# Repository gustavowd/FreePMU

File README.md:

# FreePMU

A Low-Cost, Open Architecture, Synchronized Harmonic Phasor Measurement Unit.

The FreePMU project delivers an open source Phasor Measurement Unit (PMU) for power system analysis based on the STM32F769 Discovery kit and an instrumentation PCB. Its characteristics are low cost, open architecture and open source code. FreePMU measures fundamental and harmonic synchrophasors as well as the signal frequency for a three-phase distribution circuit.

Prototype

# Publications

SEGER, P. V. H.; MORETO, MIGUEL; GRANDO, F. L.; LAZZARETTI, A. E.; DENARDIN, G. W.; PASTRO, C. R. Power System Monitoring Through Low-Voltage Distribution Network Using freePMU. IEEE Transactions on Industry Applications, v. 58, n. 3, p. 3153-3163, 2022.

SEGER, P. V. H.; MORETO, MIGUEL; GRANDO, F. L.; LAZZARETTI, A. E.; DENARDIN, G. W.; PASTRO, C. R. Monitoring Low Voltage Electrical Networks Using Low Cost PMUs: a Case Study. IEEE International Conference on Environment and Electrical Engineering and IEEE Industrial and Commercial Power Systems Europe, 2020, Madrid.

GRANDO, F. L.; DENARDIN, G. W.; MORETO, M.; LAZZARETTI, A. E.; VIEIRA NETO, H. A method for synchronized harmonic phasor measurement based on hardware-enhanced Fast Fourier Transform. International Transactions on Electrical Energy Systems, v. 30, p. 1-19, 2020.

# Configurations

The PMU code has several possible configurations. These settings can be configured in the main.h file.

1. Set the PMU identification number for the communication with PDC

#define PMUID	0x0001

2. Set the utility nominal frequency (50 or 60Hz)

#define NOMINAL_FREQ 60

3. Set the utility nominal voltage (127 or 220V)

#define NOMINAL_VOLTAGE 127

4. Define if harmonics are enable or not

#define ENABLE_HARMONICS 1

5. Set if the oversamling will be used or not (0 or 1)

#define OVERSAMPLING 1

6. Define the GPS baudrate

#define GPS_BAUDRATE 115200

7. Set this define to 1 for simulate GPS time stamp and PPS

#define SIMULATED_GPS 0

8. Defines if the GPS will provide the 30 pulses per second or not (if not defined, GPS will provide 1 pulse per second)

#define PPS_30_HZ

9. Defines if the measure data will be based on peak or RMS values (possible values are RMS_GAIN or PEAK_GAIN)

#define PEAK_OR_RMS	RMS_GAIN

10. Set the transport protocol to communicate with the PDC (TCP_PMU or UDP_PMU)

#define TRANSPORT_PROTOCOL TCP_PMU

11. Several gains for the fit curves (depends on the instrumentation board)

For better performance, such gains must be defined through a calibration process

Interface video

Connections

Used GPS

Used voltage transformer

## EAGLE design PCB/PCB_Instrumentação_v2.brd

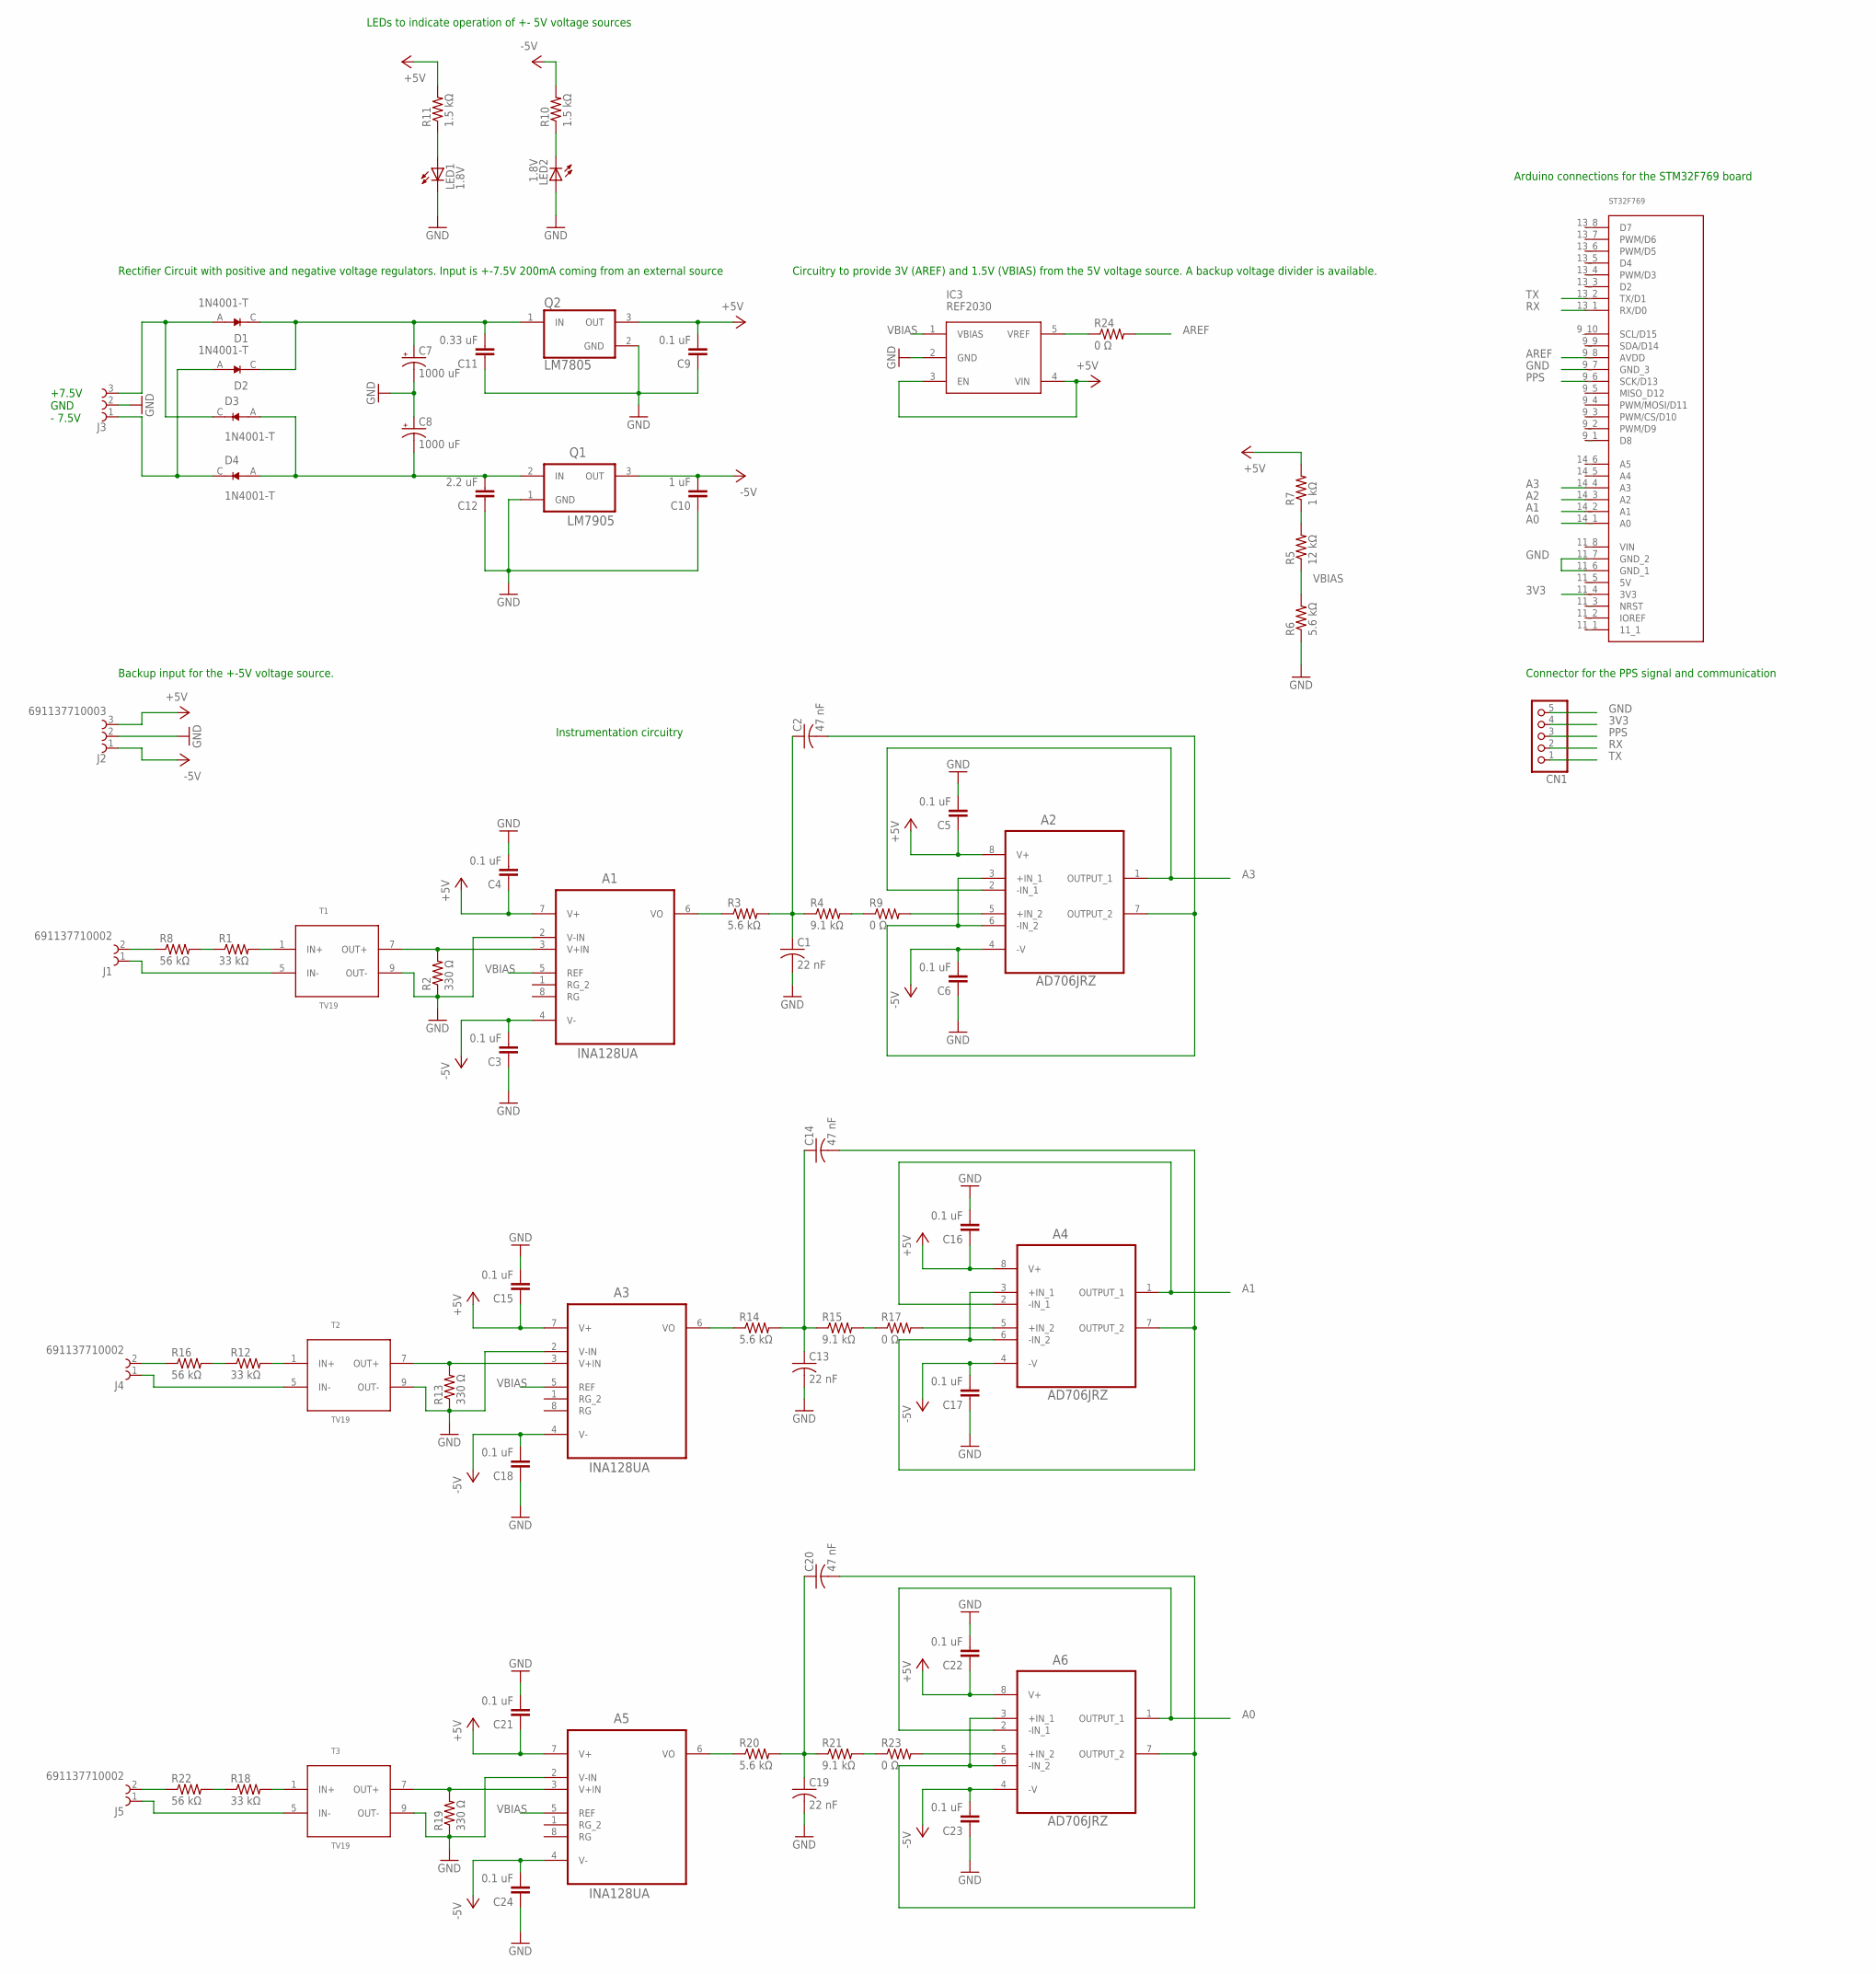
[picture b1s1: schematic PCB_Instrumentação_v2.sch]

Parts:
A1, A3, A5: INA128UA; SOIC127P600X175-8N
A2, A4, A6: AD706JRZ; SOIC127P600X175-8N
C1, C13, C19: 22 nF; C1206
C2, C14, C20: 47 nF; C1206
C3, C4, C5, C6, C9, C15, C16, C17, C18, C21, C22, C23, C24: 0.1 uF; C0805
C7, C8: 1000 uF; E5-10,5
C10: 1 uF; C0805
C11: 0.33 uF; C0805
C12: 2.2 uF; C0805
CN1: PINHD-1X5; 1X05
D1, D2, D3, D4: 1N4001-T; DIOAD953W69L521D272
IC3: REF2030; TSOT-23_S5
J1, J4, J5: 691137710002
J2, J3: 691137710003
LED1, LED2: 1.8V; LED5MM
Q1: LM7905; TO254P450X1020X1935-3P
Q2: LM7805; TO254P1054X470X2600-3
R1, R12, R18: 33 kΩ; 0207/7
R2, R13, R19: 330 Ω; 0207/7
R3, R6, R14, R20: 5.6 kΩ; R1206
R4, R15, R21: 9.1 kΩ; R1206
R5: 12 kΩ; R1206
R7: 1 kΩ; R1206
R8, R16, R22: 56 kΩ; 0207/7
R9, R17, R23, R24: 0 Ω; R1206
R10, R11: 1.5 kΩ; R1206
T1, T2, T3: TV19
U$1: ST32F769

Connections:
3V3: CN1.4, U$1.11_4 (3V3)
+5V: A1.7 (V+), A2.8 (V+), A3.7 (V+), A4.8 (V+), A5.7 (V+), A6.8 (V+), C4.1, C5.1, C9.2, C15.1, C16.1, C21.1, C22.1, IC3.3 (EN), IC3.4 (VIN), J2.3, Q2.3 (OUT), R7.2, R11.2
-5V: A1.4 (V-), A2.4 (-V), A3.4 (V-), A4.4 (-V), A5.4 (V-), A6.4 (-V), C3.2, C6.2, C10.2, C17.2, C18.2, C23.2, C24.2, J2.1, Q1.3 (OUT), R10.2
A0: A6.1 (OUTPUT_1), A6.2 (-IN_1), U$1.14_1 (A0)
A1: A4.1 (OUTPUT_1), A4.2 (-IN_1), U$1.14_2 (A1)
A2: U$1.14_3 (A2)
A3: A2.1 (OUTPUT_1), A2.2 (-IN_1), U$1.14_4 (A3)
AREF: R24.2, U$1.9_8 (AVDD)
GND: A1.2 (V-IN), A3.2 (V-IN), A5.2 (V-IN), C1.2, C3.1, C4.2, C5.2, C6.1, C7.-, C8.+, C9.1, C10.1, C11.1, C12.1, C13.2, C15.2, C16.2, C17.1, C18.1, C19.2, C21.2, C22.2, C23.1, C24.1, CN1.5, IC3.2 (GND), J2.2, J3.2, LED1.K (C), LED2.A, Q1.1 (GND), Q2.2 (GND), R2.1, R6.1, R13.1, R19.1, T1.9 (OUT-), T2.9 (OUT-), T3.9 (OUT-), U$1.9_7 (GND_3), U$1.11_6 (GND_1), U$1.11_7 (GND_2)
unnamed: R1.2, T1.1 (IN+)
unnamed: A1.3 (V+IN), R2.2, T1.7 (OUT+)
unnamed: A1.6 (VO), R3.1
unnamed: C1.1, C2.1, R3.2, R4.1
unnamed: R4.2, R9.1
unnamed: A2.3 (+IN_1), A2.6 (-IN_2), A2.7 (OUTPUT_2), C2.2
unnamed: R5.2, R7.1
unnamed: J1.2, R8.1
unnamed: J1.1, T1.5 (IN-)
unnamed: R1.1, R8.2
unnamed: C7.+, C11.2, D1.C, D2.C, Q2.1 (IN)
unnamed: C8.-, C12.2, D3.A, D4.A, Q1.2 (IN)
unnamed: D2.A, D4.C, J3.1
unnamed: D1.A, D3.C, J3.3
unnamed: A2.5 (+IN_2), R9.2
unnamed: LED1.A, R11.1
unnamed: LED2.K (C), R10.1
unnamed: R12.2, T2.1 (IN+)
unnamed: A3.3 (V+IN), R13.2, T2.7 (OUT+)
unnamed: A3.6 (VO), R14.1
unnamed: C13.1, C14.1, R14.2, R15.1
unnamed: A4.3 (+IN_1), A4.6 (-IN_2), A4.7 (OUTPUT_2), C14.2
unnamed: J4.1, T2.5 (IN-)
unnamed: J4.2, R16.1
unnamed: R12.1, R16.2
unnamed: R15.2, R17.1
unnamed: A4.5 (+IN_2), R17.2
unnamed: R18.2, T3.1 (IN+)
unnamed: A5.3 (V+IN), R19.2, T3.7 (OUT+)
unnamed: A5.6 (VO), R20.1
unnamed: C19.1, C20.1, R20.2, R21.1
unnamed: A6.3 (+IN_1), A6.6 (-IN_2), A6.7 (OUTPUT_2), C20.2
unnamed: J5.1, T3.5 (IN-)
unnamed: J5.2, R22.1
unnamed: R18.1, R22.2
unnamed: R21.2, R23.1
unnamed: A6.5 (+IN_2), R23.2
unnamed: IC3.5 (VREF), R24.1
PPS: CN1.3, U$1.9_6 (SCK/D13)
RX: CN1.2, U$1.13_1 (RX/D0)
TX: CN1.1, U$1.13_2 (TX/D1)
VBIAS: A1.5 (REF), A3.5 (REF), A5.5 (REF), IC3.1 (VBIAS), R5.1, R6.2

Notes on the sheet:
LEDs to indicate operation of +- 5V voltage sources
Rectifier Circuit with positive and negative voltage regulators. Input is +-7.5V 200mA coming from an external source
Circuitry to provide 3V (AREF) and 1.5V (VBIAS) from the 5V voltage source. A backup voltage divider is available.
Arduino connections for the STM32F769 board
Backup input for the +-5V voltage source.
Connector for the PPS signal and communication
Instrumentation circuitry
+7.5V GND - 7.5V

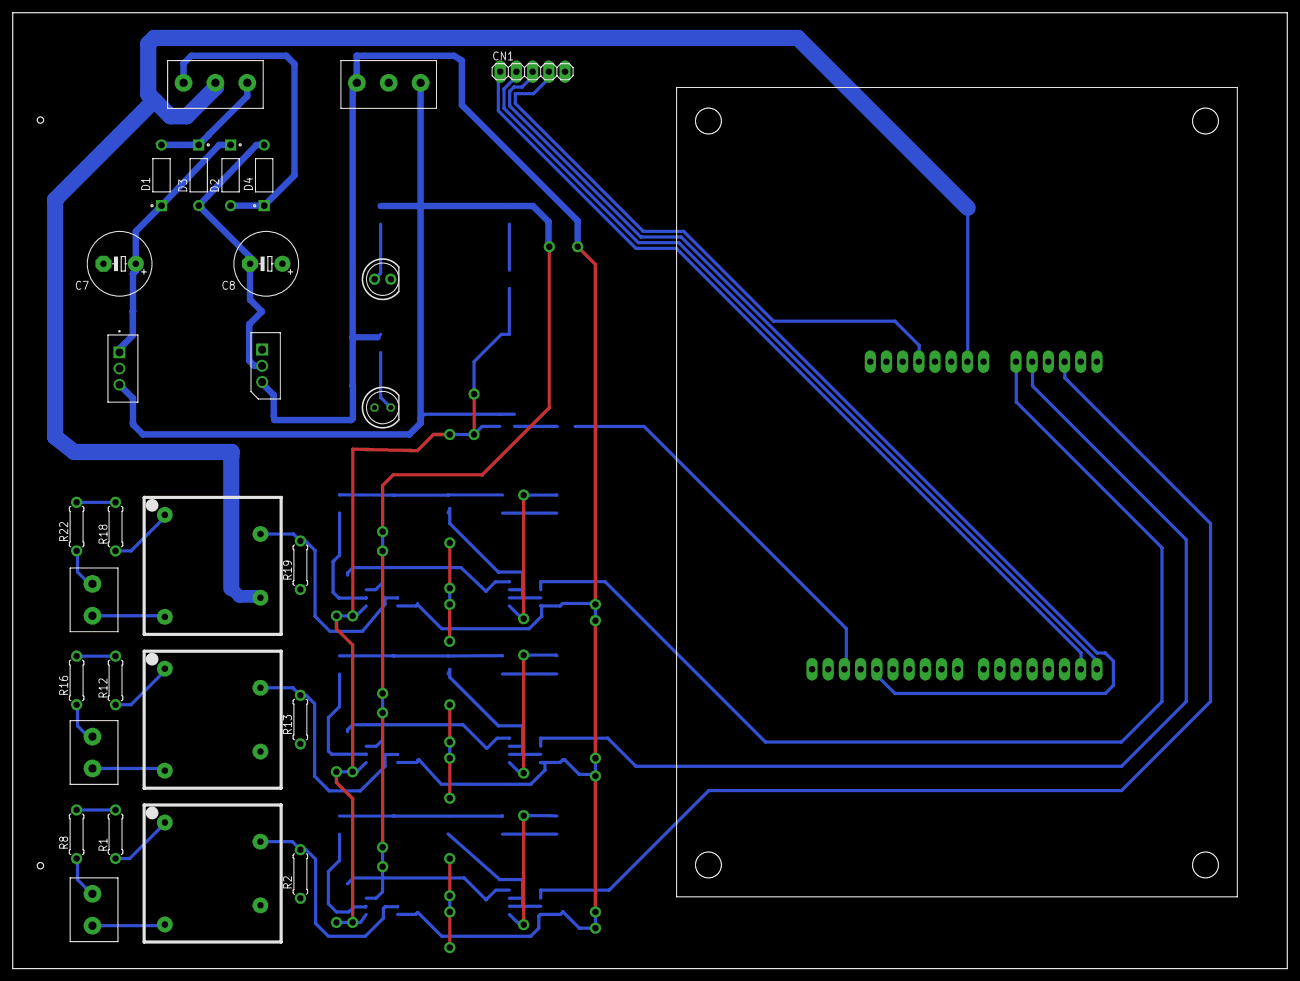
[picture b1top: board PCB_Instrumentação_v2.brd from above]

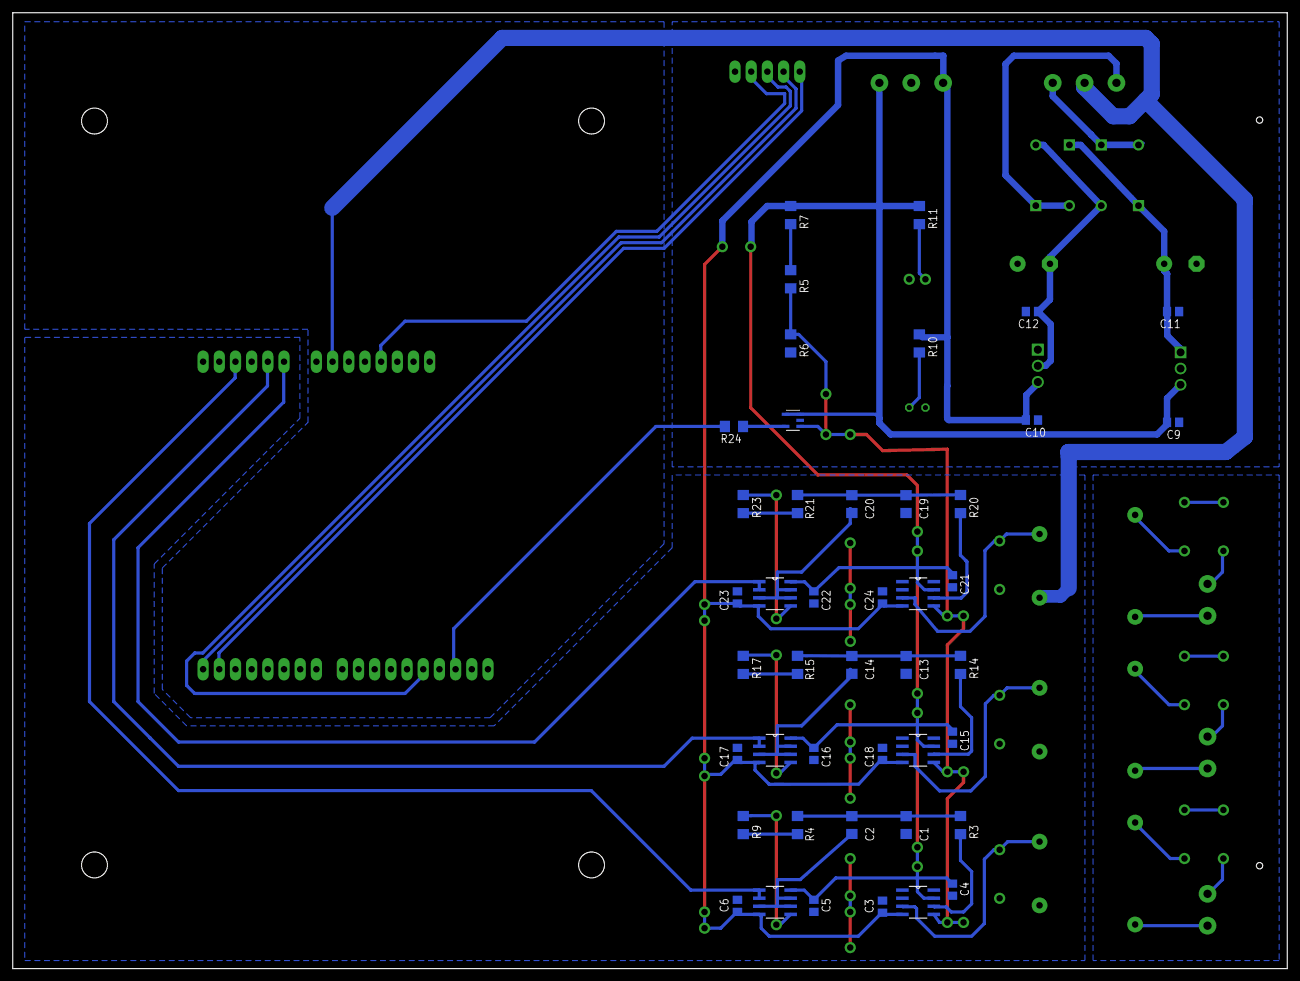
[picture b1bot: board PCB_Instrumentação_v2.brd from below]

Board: 2 copper layers, 200.0 x 150.0 mm, 73 parts (44 on the bottom side), 50 nets.

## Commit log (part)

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2018-05-18 Primeira versão do projeto no gitlab
2018-05-18 Adicionado código da FFT
2018-05-18 Adicionado o projeto do Embedded Wizard
2018-05-19 Correção no link das imagens
2018-05-24 Inserção da tela de FFT e anotações dos métodos dentro do auto-objeto. Organização das cores dos fasores em constantes. Também foi inserido uma variante do Action Button, chamado ModifiedButton, que 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
2018-05-24 Atualização dos arquivos gerados pelo Embedded Wizard a partir do seguinte commit: https://gitlab.com/gustavowd78/PMU_EmbeddedWizard/commit/88e431ba136419b750d649c0055825b5b472bed3.
2018-05-28 Adicionado projeto do STM32F769
2018-05-28 Correção das inclusões de pastas de includes.
2018-05-28 Modificação do clock para 200 MHz. Habilitados somente 3 canais de ADC. Mudança do TIM1 para o TIM2 no trigger do ADC.
2018-05-28 Corrigidos textos da tela do servidor
2018-05-28 Corrigidas mensagens e ações do servidor de dados para o PDC
2018-05-28 Corrigido tamanho da tela para o 769, os textos do servidor no 746 e o texto inferior da parte do servidor para ambos.
2018-05-29 Acerto da interface na tela de 800x472. Volta do timer para TIM1 / trigger PA12
2018-05-29 Correção para 256 amostras em 60 Hz
2018-05-30 Modificação dos valores de exibição de fase e magnitude.
2018-05-30 USART1 configurada para funcionar com interrupção. Transmissão dos dados adquiridos pela serial.
2018-05-30 Correção da interface gráfica para a FFT e para mostrar as fases de -180 a 180 graus.
2018-06-05 Adicionado projeto teste do 746.
2018-06-06 Pequenos testes na PMU com o STM32F769
2018-06-06 PMU funcionando com o 746.
2018-06-07 Adicionado suporte a porta serial pela USB no kit STM32F746
2018-06-12 Atualização dos gráficos atualizada para 100ms
2018-06-13 Mudança de endereço da SDRAM utilizada para framebuffer de 0xC0000000 para 0x60000000, pois essa faixa de endereço é cacheable.
2018-06-14 Atualização do servidor PDC para o 769 e aumento do heap do FreeRTOS
2018-06-14 Mais correções para o servidor PDC no STM32F769
2018-06-14 Mudanças para corrigir erros de conexão com o cliente PDC
2018-06-19 Projeto de teste alterado com o TIM2 disparando a 30 Hz e suporte a porta serial adicionado.
2018-06-19 Adicionado disparo do TIM8 pelo TIM2 no projeto do 746.
2018-06-20 Mudança para disparar o TIM2 pelo pino PA0 (botão do kit) no 769
2018-06-20 Pequena correção na posição do código para troca de estado do LED na interrupção de DMA
2018-06-21 Testes para melhorar o desempenho da pmu com o timer de 30 hz
2018-06-21 Mudança da frequencia para 210 MHz na correção do clock
2018-06-21 Correção de um pequeno erro
2018-06-21 Habilitada interrupção da tim2 para avaliar o sincronismo. Corrigido clock do lcd.
2018-06-24 Atualização dos arquivos de plataforma embedded wizard para a versão 9.0 no STM32F769
2018-06-24 Adicionado função ButtonStatus para alterar o estado dos botões Iniciar e Parar na tela de servidor.
2018-06-24 Atualizado arquivos de aplicação da interface e bibliotecas do Embedded Wizard para versão 9.0 para o 746.
2018-06-24 Adicionado função do estado dos botões no projeto do 769.
2018-06-24 Adicionado arquivos faltantes na pasta EmbeddedWizardApp do projeto do 769
2018-06-25 Adicionados arquivos faltantes para compilar aplicação embedded wizard no projeto do STM32F769.
2018-06-25 Última versão da aplicação nos projetos dos STM32F7
2018-06-25 Adicionado teste de valor residual na taxa de amostragem para definir o valor mais próximo do idel. Adicionado controle do botão start e stop do servidor PDC pelo código.
2018-06-29 Mudança no tim2 para fazer um deinit e depois inicializar novamente a cada 30 pulsos
2018-07-02 Mudança no tamanho dos ícones no projeto do Embedded Wizard em ambas as plataformas.
2018-07-03 Icone de configuração aumentado.
2018-07-05 Sobreamostragem de 4x e média a cada 4 pontos para melhorar a resposta do ADC a erros aleatórios (distribuição normal)
2018-07-09 Adicionado buffer do ADC na memória DTCM. Remoção da sobreamostragem com média. Aumento do clock do ADC.
2018-07-09 As seguintes correções do 769 foram aplicadas no projeto do 746: - Clock da MCU de 200 para 210MHz - Timers para refletir a mudança de clock - Prioridade das interrupções - Clock do LCD
    Foi adicionado:
    - Valor residual taxa de amostragem
    - Sobreamostragem de 4 vezes
    - ADCBuffer na DTCM
2018-07-11 PMU com o STM32F769 com sobreamostragem de 4x e média para filtrar ruídos da aquisição.
2018-07-12 Correção na média dos pontos sobreamostrados. Aumento da sobreamostragem para 8 pontos.
2018-07-12 Melhorias da média do projeto do 746
2018-07-20 Pequena correção para o TIM2 em 60 Hz
2018-07-23 Embedded Wizard: Botões para alterar a frequência base no gráfico de frequência - 50, 55 e 60Hz. Adicionada taxa de amostragem de 25Hz.
2018-07-24 Frequencia central padrão definida como 50 Hz. Taxa de atualização padrão 25 fps.
2018-07-25 Correção do bug de escala na inicialização do gráfico de frequência.
2018-07-25 Atualização da interface gráfica para a versão com correção de escala inicial.
2018-12-06 Correções no código do STM32F746.
2019-02-13 Alterações em arquivos auxiliares
2019-02-13 Refatorado trechos do código
    -> Função "MX_USART1_UART_Init() removida, não era utilizada pra nada.
    -> Haviam as funções "UARTPutString()" e "SerialSend()" declaradas em um #if 0 na main.c. Removidas
    -> Foram removidas declarações de "if EW_USE_FREE_RTO". Por padrão sempre usará FreeRTOS
    -> Removida a declaração da função "CalculaMediaADC(uint16*)", esta função não existe.
    -> Removida a declaração da função " SSL_Client(void const*), esta função existe no arquivo ssl_client.c, mas nunca é
    chamada. Quando for utilizar, chamar a biblioteca.
2019-04-02 Corrigida a recepção do SOC
    O GPS envia vários pacotes com dados. Anteriormente, era suposto que o GPS enviava um pacote com o dia da semana. Este pacote era usado para calcular o SOC. Porém, não havia qualquer verificação do p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
2019-04-04 Correção de pequenos erros
    Alguns pequenos erros foram corrigidos. A PMU finalmente está enviando dados, os quais estão sendo recebidos pelo PMUConectionTester
2019-04-16 Correção do Fraction of second
    Fraction of second era colocado de modo descincronizado nos dados enviados, de modo que o primeiro frame de cada SOC não necessarimente continha um Fraction of second=0.
    Corrigido.
2019-05-02 Correção do uso dos Timers pro 762
    O código tentava trigar o TIM1 pelo TIM8, porém isso não é possível. Agora o TIM8 triga o TIM1.
    Além disso, o pino usado para fazer o Trigger já estava sendo usado.
2019-05-22 Removendo as pastas com objetos compilados
2019-05-22 correção na inclusão do arquivo tarefasPMU.h
2019-05-27 Modificado dhcp_client.c para suportar IP fixo. Para isso foi adicionado um #ifdef no arquivo.
2019-05-27 Correção na transmissão de dados para a plataforma de testes
2019-05-29 Adicionado suporta a PPS com 30 Hz. Substituição de valores por defines em alguns calculos.
2019-05-29 Pequena correção no código de incremento do FracSec
2019-05-29 Correções no fracSec
2019-05-30 Adicionado suporte aos protocolos NMEA e UBX para o GPS com escolha por define.
2019-05-30 Correção no código de escolha dos protocolos do GPS
2019-05-30 Validação do pacote NMEA recebido
    Além de verificar se o pacote recebido é o GPRMC, verificou-se se foi recebido todas as informações necessárias para o cálculo do SOC. Caso a data não for recebida, usa-se a última data válida. Caso 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
2019-05-30 Código para decodificar NMEA corrigido.
2019-05-30 Corrigido tamanho do buffer da mensagem GPS para nmea.
2019-05-31 Limpeza do código
2019-05-31 Mudança do pino de trigger na versão com PPS de 30Hz para PA12 (D13)
2019-05-31 Correção na definicao de trigger por timer para o ADC com PPS de 30 Hz
2019-05-31 Modificados valores default dos gráficos da GUI para 60Hz e 220V.
2019-06-04 Adicionado pino para ligar o GPS
    O pino PJ1 foi utilizado para ligar o GPS. Quando o micro for reiniciado, os PPS podem não ser interrompidos. Isso acaba provocando uma desincronização da medição fasorial com os SOCs corretos.
2019-06-04 Documentação Adicionada
    Apenas foi adicionada a documentação do kit F769
2019-06-13 Corrigida soncronização do SOC com o PPS na versão de 30 Hz
    Verificou-se que quando o GPS está configurado para 30 Hz, o SOC é enviado antes do primeiro PPS.
2019-08-23 Corrigido variações na frequencia
2019-08-23 Adicionados defines para configurar o ajuste de frequencia e do timer
2021-03-18 Pacote de dados agora transmite fundamental e 10 harmônicas.
2021-03-19 Removidos arquivos desnecessários.
2021-03-19 Removidos arquivos desnecessários 2.
2021-03-19 Adicionada imagem do TV19
2021-03-21 Corrigido tamanho de pacotes de mensagens na função de checksum para 16 bits
2021-03-21 Corridiga declaração de variável como uint 16 bits
2021-03-22 Correções para deixar o código da comunicação e GPS mais genérico para 50/60Hz e diferentes tamanhos de pacotes de dados.
2021-03-22 Correção de travamento com adição de mutex. Correção da transmissão de dados com fasores.
2021-03-22 Adicionados arquivos da PCI.
2021-03-23 Adicionado projeto da interface gráfica.
2021-03-24 Correções no gráfica das harmônicas.
2021-03-24 Adicionados ganhos para as harmônicas serem mostradas normalizadas em relação a 127 ou 220V
2021-03-24 Correção na magnitude das fundamentais.
2021-03-24 Adicionada configuração para a tensão RMS padrão (127 ou 220V)
2021-03-24 Adicionadas as configurações .h das duas PMUs de teste. Suporte a 4 ganhos para a fase.
2021-03-26 Projeto da interface gráfica atualizado
2021-03-26 Adicionado envio de harmônica nas três fases. Adicionado cálculo de THD. Adicionado reconhecimento automático do tipo de pacote do módulo GPS. Correção no tamanho do pacote de dados para a fila de me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
2021-03-28 Correção na decodificação do pacote GPS e na fase das harmônicas.
2021-03-29 Correção para enfileirar o tamanho correto de pacotes. Adicionada proteção contra estouro de memória ao enfileirar muitos pacotes sem newSOC.
2021-03-29 Adicionada imagem com conexões.
2021-03-30 Corrigido erro de harmônicas superiores a 20% (imprimia um warning no terminal). Adicionada configuração para habilitar/desabilitar harmonicas na transferencia para o PDC.
2021-03-30 Correção de harmônicas fora do gráfico nas fases S e T.
2021-03-31 Adicionada possibilidade de simular o GPS com estampa de tempo e PPS
2021-04-01 Correção na frequencia do PPS do GPS simulado.
2021-04-02 PMU agora inicia o servidor TCP/UDP no boot
2021-04-06 Alterada prioridade da tarefa DHCP. A tarefa do GPS deve ter maior prioridade que o DHCP e a comunicação.
2021-04-06 Adicionada configuração do baudrate do GPS no arquivo main.h
2021-04-07 Adicionado configuração para transmitir somente os fasores das harmônicas da primeira fase. Compatibilidade para o openPDC
2021-04-15 Adicionada possibilidade de enviar dados de fasores pela porta serial.
2021-04-15 Adicionado código em python para receber os dados da PMU pela porta serial.
2021-09-17 First version of PMU v2.0.0
2021-09-17 removidos os arquivos dos projetos anteriores
2021-09-19 Added harmonics chart
2021-09-20 GPS info bug correction
2021-09-21 improvements in the GUI DHCP status
2021-11-16 Update README.md
    Figura atualiza da PMU
2021-11-16 Update README.md
    Adicionado principais publicações
2021-11-23 Added device specific include files for defining the calibration gains.
2021-11-23 Removing Debud folder from the repository.
2022-01-20 Added MAC address definition in the PMU device specific header files. Updated PMU ID definition and specific header files selection procedure.
2022-01-20 Updated GUI to show PMU ID. Starting to write functions tu show in the GUI the current GPS timestamp.
2022-01-20 Added timestamp in the GUI.
2022-02-05 Added timeout support when sending data through sockets. TCP/IP task stack increased by 128 words.
2022-02-05 Idle task stack increased by 128 words.
2022-02-05 Same priority set to in/out IEEE Std C37.118 network tasks.
2022-02-07 Added print server. Several improvements in the network code. New sync scheme for GPS/data packets.
2022-02-08 Memory increase of the TCP/IP stack send buffer
